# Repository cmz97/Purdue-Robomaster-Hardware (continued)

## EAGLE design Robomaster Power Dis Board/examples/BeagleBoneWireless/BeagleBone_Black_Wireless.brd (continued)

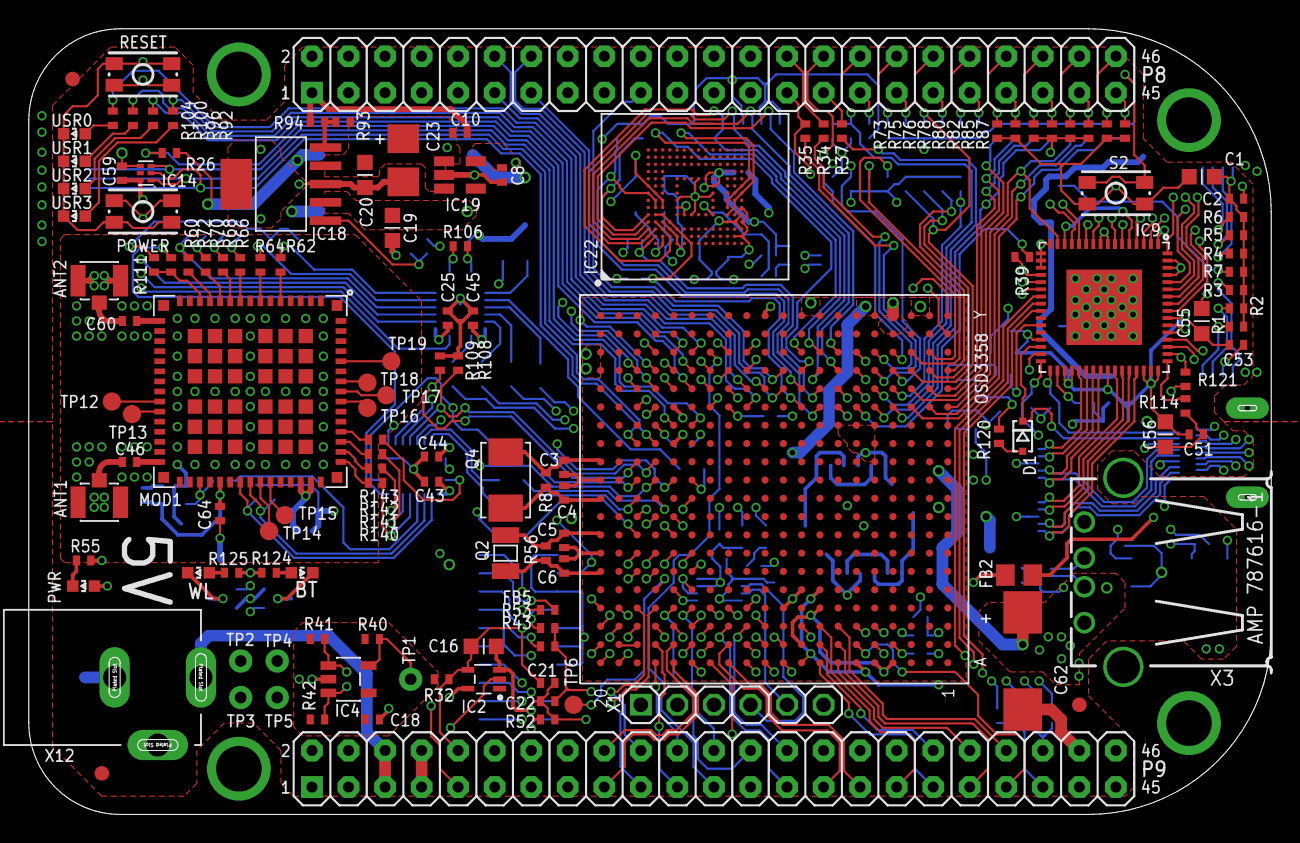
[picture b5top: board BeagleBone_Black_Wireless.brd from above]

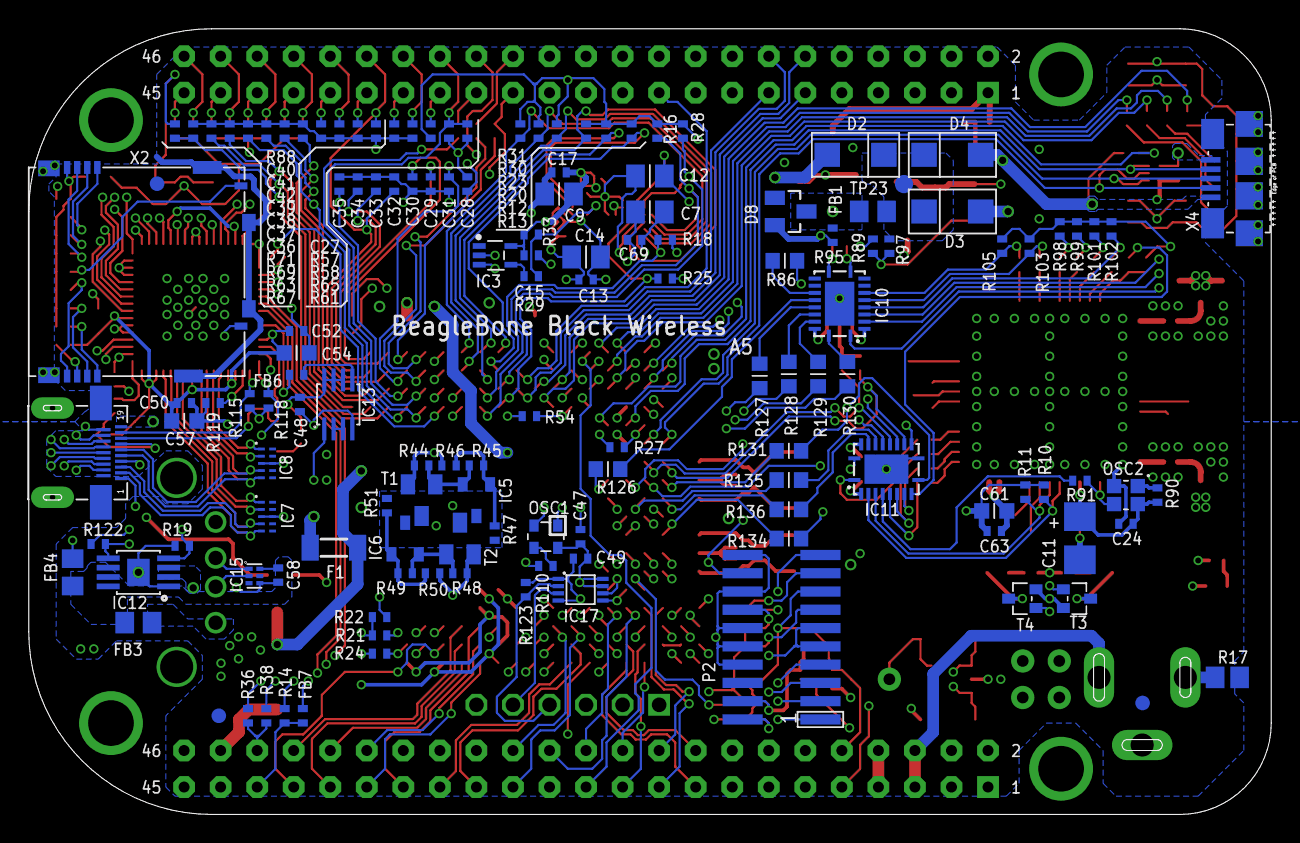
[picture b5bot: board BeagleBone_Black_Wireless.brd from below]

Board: 6 copper layers, 86.4 x 54.6 mm, 275 parts (139 on the bottom side), 262 nets.

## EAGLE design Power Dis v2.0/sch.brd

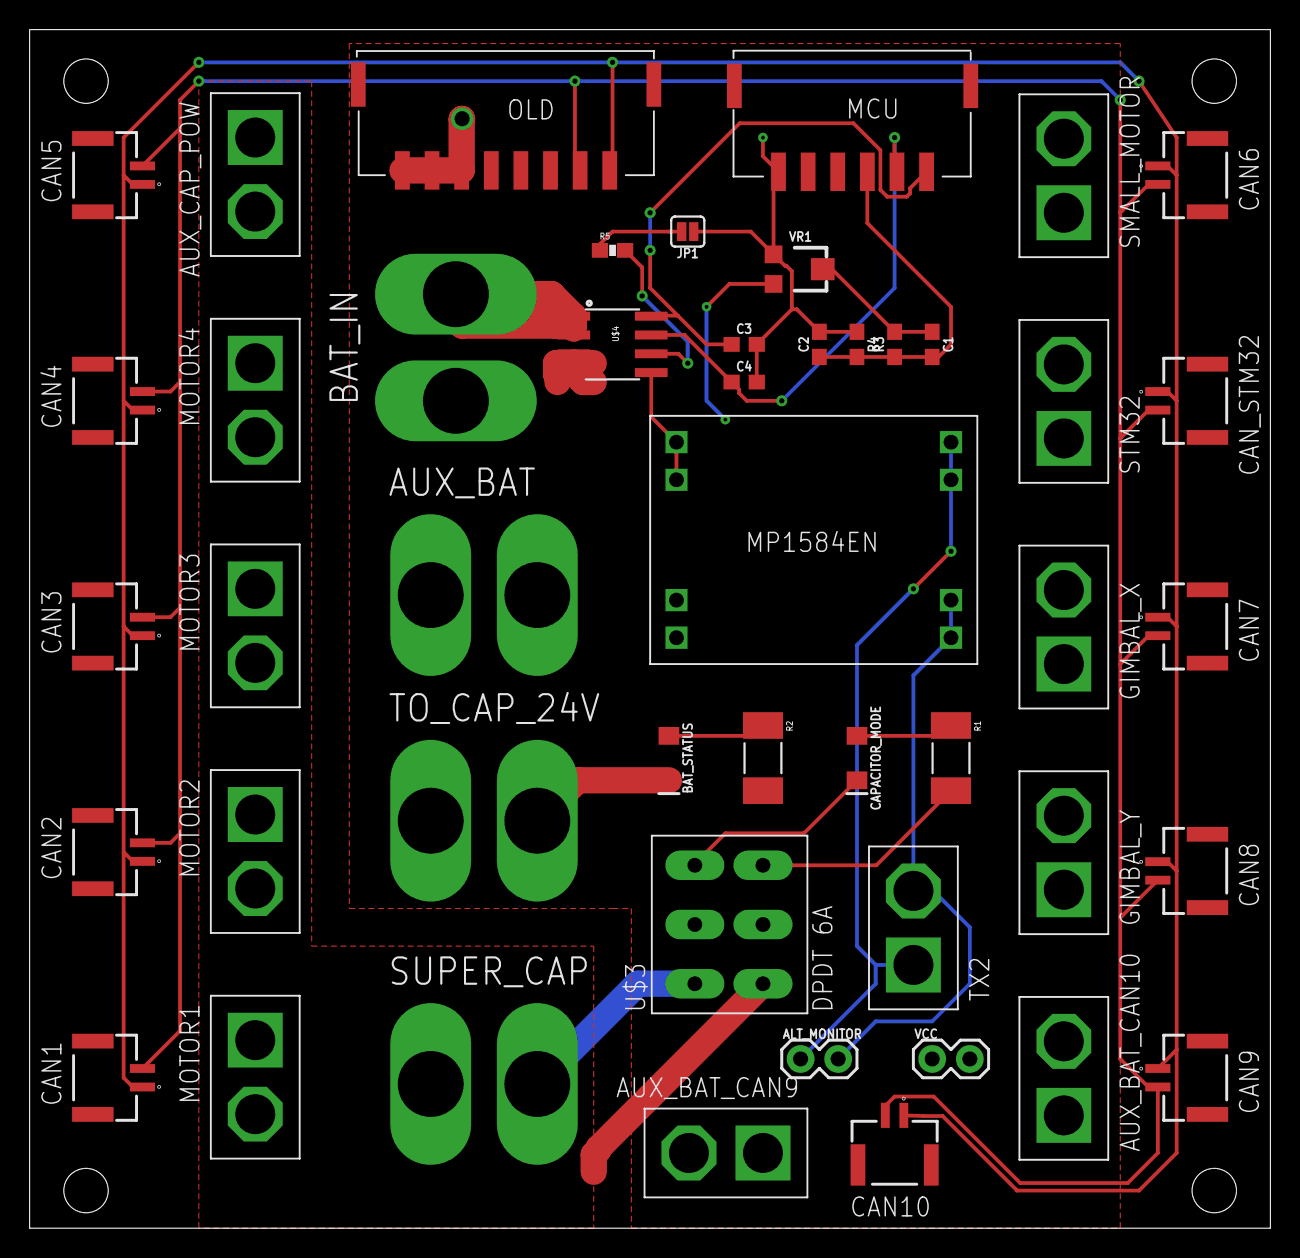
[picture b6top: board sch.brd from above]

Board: 2 copper layers, 83.8 x 81.0 mm, 47 parts (0 on the bottom side), 19 nets.

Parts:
ALT_MONITOR: 1X02
AUX_BAT: XT60
AUX_BAT_CAN9, AUX_BAT_CAN10: XT30
AUX_CAP_POW: XT30
BAT_IN: XT60
BAT_STATUS: 3V 20mA; LED-1206
C1, C2, C3: 0.1uF; 0603
C4: 1nF; 0603
CAN1, CAN2, CAN3, CAN4, CAN5, CAN6, CAN7, CAN8, CAN9, CAN10: BM02B-GHS-TBT(LF)(SN); BM02B-GHS-TBT_1
CAN_STM32: BM02B-GHS-TBT(LF)(SN); BM02B-GHS-TBT_1
CAPACITOR_MODE: 3V 20mA; LED-1206
GIMBAL_X: XT30
GIMBAL_Y: XT30
JP1: JUMPER-SMT_2_NO_SILK; SMT-JUMPER_2_NO_SILK
MCU: S6B-PH-SM4_TB
MOTOR1, MOTOR2, MOTOR3, MOTOR4: XT30
OLD: S8B-PH-SM4_TB
R1, R2: 1.2K; R2010
R3: 10k; 0603
R4: 2.0k; 0603
R5: 4.7K; 0603-RES
SMALL_MOTOR: XT30
STM32: XT30
SUPER_CAP: XT60
TO_CAP_24V: XT60
TX2: XT30
U$2: MP1584; MP1584_AMAZON
U$3: DPDT
U$4: ACS723; SO08
VCC: 1X02
VR1: 10k; TRIMPOT-SMD-TC33X

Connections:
ALT_GND: ALT_MONITOR.1, TX2.P$1, U$2.5, U$2.6
ALT_VCC: ALT_MONITOR.2, TX2.P$2, U$2.7, U$2.8
ANALOG_OUT: C1.2, C2.1, MCU.3, R3.1, R4.2
BAT_24V: AUX_BAT.1, AUX_BAT_CAN9.P$2, AUX_BAT_CAN10.P$2, GIMBAL_X.P$2, GIMBAL_Y.P$2, OLD.3, OLD.4, OLD.5, R2.2, SMALL_MOTOR.P$2, STM32.P$2, TO_CAP_24V.1, U$2.3, U$2.4, U$3.P$2, U$4.3, U$4.4, VCC.2, VR1.3
BAT_GND: AUX_BAT.2, AUX_BAT_CAN9.P$1, AUX_BAT_CAN10.P$1, BAT_IN.2, BAT_STATUS.C, C2.2, C3.2, C4.2, GIMBAL_X.P$1, GIMBAL_Y.P$1, JP1.1, MCU.6, OLD.6, OLD.7, OLD.8, R4.1, SMALL_MOTOR.P$1, STM32.P$1, TO_CAP_24V.2, U$2.1, U$2.2, U$3.P$5, U$4.5, VCC.1, VR1.1
BAT_IN: BAT_IN.1, U$4.1, U$4.2
BW_SEL: R5.2, U$4.6
CANH: CAN1.2, CAN2.2, CAN3.2, CAN4.2, CAN5.2, CAN6.2, CAN7.2, CAN8.2, CAN9.2, CAN10.2, CAN_STM32.2, OLD.2
CANL: CAN1.1, CAN2.1, CAN3.1, CAN4.1, CAN5.1, CAN6.1, CAN7.1, CAN8.1, CAN9.1, CAN10.1, CAN_STM32.1, OLD.1
CAP_24V: AUX_CAP_POW.P$2, MOTOR1.P$2, MOTOR2.P$2, MOTOR3.P$2, MOTOR4.P$2, SUPER_CAP.1, U$3.P$1
CAP_GND: AUX_CAP_POW.P$1, MOTOR1.P$1, MOTOR2.P$1, MOTOR3.P$1, MOTOR4.P$1, SUPER_CAP.2, U$3.P$4
MCU_VCC: C3.1, MCU.1, U$4.8
unnamed: R1.2, U$3.P$3
unnamed: CAPACITOR_MODE.A, R1.1
unnamed: CAPACITOR_MODE.C, U$3.P$6
unnamed: JP1.2, R5.1
unnamed: BAT_STATUS.A, R2.1
unnamed: C1.1, R3.2, VR1.2
VIOUT: C4.1, MCU.2, U$4.7

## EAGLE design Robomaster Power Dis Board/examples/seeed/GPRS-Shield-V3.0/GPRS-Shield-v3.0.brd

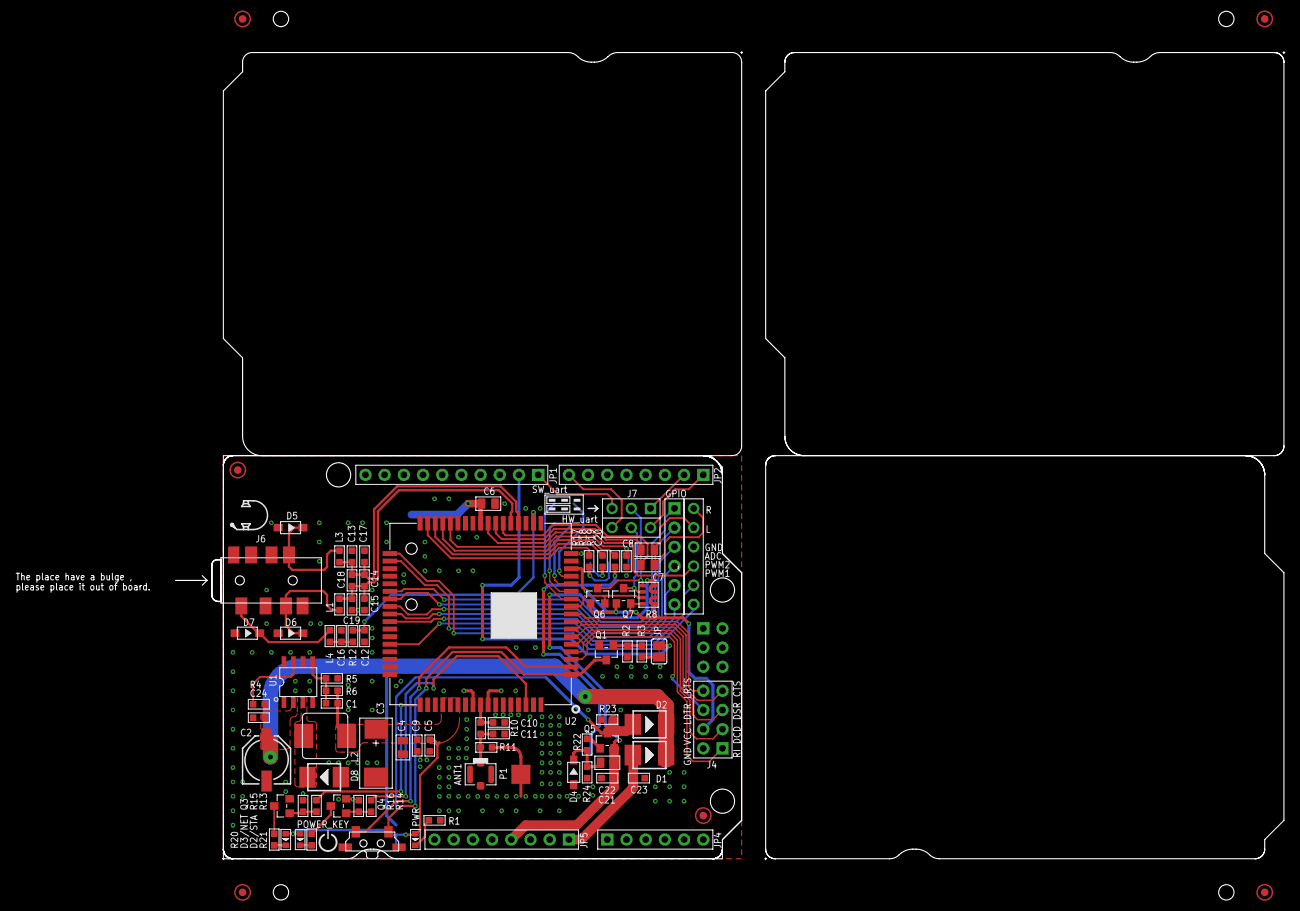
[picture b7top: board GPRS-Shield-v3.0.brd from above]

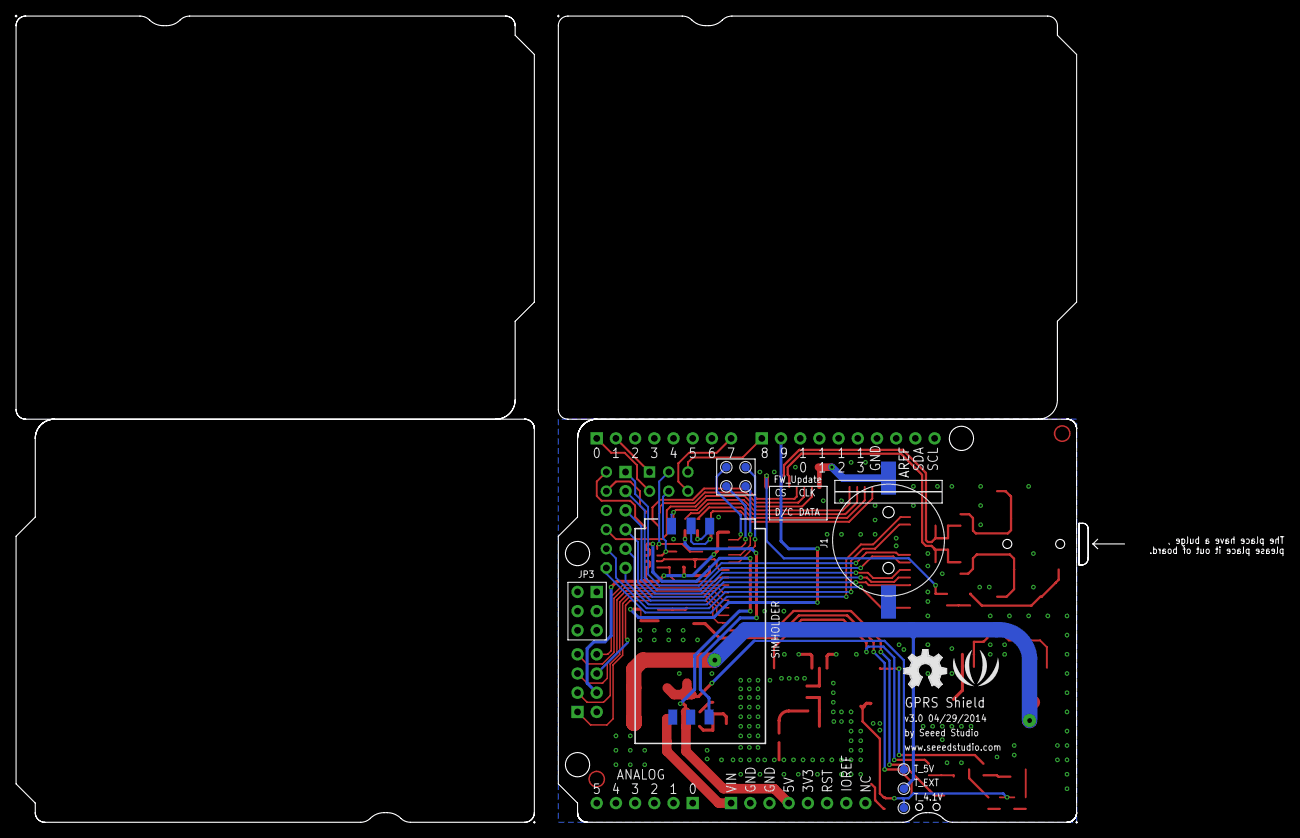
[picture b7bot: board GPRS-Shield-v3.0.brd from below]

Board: 2 copper layers, 146.8 x 106.9 mm, 95 parts (11 on the bottom side), 74 nets.

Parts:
ANT1: 4P-U-FL
C1, C10, C11: DNP; C0603
C2: 16V 220uF; ELECTRO-SMD-D-5.6MM
C3: 470uF; AVX-D
C4, C22: 10uF; C0805
C5, C9, C21, C23, C24: 100nF; C0603
C6: 4.7u; C0805
C7, C8: 2.2u; C0805
C12, C16, C17, C18, C19: 39pF; C0603
C13, C14, C15: 8.2pF; C0603
C20: 100n; C0603
CLK: TP_4545
CS: TP_4545
D1, D2, D8: SS54; SMB
D2/STA: red; D0603
D3/NET: green; D0603
D4: MBR0520; SOD123-2.7X1.6
D5, D6, D7: CESD5V0D1; SOD123-2.7X1.6
D/C: TP_4545
DATA: TP_4545
J1: SMD-CR1220-2
J3: 6P-2.54-65/35MIL
J4: 2X4P-2.54
J6: 8P-SMD-3.5
J7: CK_2X3_DD; CK_2X3
J13: CK_1X6
JP: 2P-SMD-3.3X2
L1, L3, L4: 120R 500mA; L0603
L2: 10uH; L0630
P1: JP
P2, P3, P4, P5, P6, P7: ROUND-MARK-1.0
POWER_KEY: BUTTON-4P-REINFORCE'TS-118E'; 4P-SMD-7X3.5X3.5H
PWR: green; D0603
Q1, Q3, Q4: 9013; SOT23
Q5: SI2305DS; SOT23
Q6, Q7: BSN20; SOT23
R1: 1k; R0603
R2, R15, R16: 47k; R0603
R3, R13, R14: 4.7k; R0603
R4: 100k; R0603
R5: 10k 1%; R0603
R6: 24k 1%; R0603
R8: 4.7k; 1206-8-3.3X2.4
R10: 0R; R0603
R11: DNP; R0603
R12: 68R; R0603
R17, R18, R19: 22R; R0603
R20, R21: 470R; R0603
R22: 100R; R0603
R23, R24: 1M; R0603
SIMHOLDER: SIMHOLDER3
T_4.1V, T_5V: TP_4545
T_EXT: TP_4545
U1: TD1410; SOP8
U2: SIM900
U4: ARDUINO-38P-500519002
U$26: LOGO_SILK
U$28: OSHW_FILLX200_NOTEXT

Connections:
5V: C21.2, C22.2, Q5.2, R8.7, R8.8, U4.28
ADC: J13.3, U2.25
CTS: J4.4, U2.7
D9: JP.1, JP.2, R3.1, U4.10
DCD: J4.2, U2.5
DISP_CLK: CLK.T, U2.11
DISP_CS: CS.T, U2.14
DISP_D/C: D/C.T, U2.13
DISP_DATA: DATA.T, U2.12
DSR: J4.3, U2.6
EXT_VIN: C23.2, D1.+, U4.25
GND: ANT1.GND1, ANT1.GND2, ANT1.GND3, C2.-, C3.-, C4.1, C5.1, C6.1, C9.1, C10.1, C11.1, C12.2, C13.2, C15.1, C16.1, C17.2, C19.1, C20.2, C21.1, C23.1, C24.1, D4.1, D5.1, D6.1, D7.1, D8.+, J1.-, J4.8, J6.2, J13.4, P1.2, POWER_KEY.S1, POWER_KEY.S2, Q1.2, Q3.2, Q4.2, R1.1, R2.2, R5.2, R15.2, R16.2, R23.2, R24.2, SIMHOLDER.6, U1.4, U2.17, U2.18, U2.20, U2.29, U2.39, U2.45, U2.46, U2.53, U2.54, U2.58, U2.59, U2.61, U2.62, U2.63, U2.64, U2.65, U4.15, U4.26, U4.27
GPIO1: J3.1, U2.40
GPIO2: J3.2, U2.41
GPIO3: J3.3, U2.42
GPIO4: J3.4, U2.43
GPIO5: J3.5, U2.44
GPIO6: J3.6, U2.47
HRXD: J7.2, Q6.3, R8.1
HTXD: J7.5, Q7.3, R8.2
LDTR: J4.6, U2.3
LINEIN_L: C8.2, U2.24
LINEIN_R: C7.2, U2.23
LRTS: J4.5, U2.8
LRXD: Q6.2, R8.3, U2.10
LTXD: Q7.2, R8.4, U2.9
MRXD: J7.1, U4.2
MTXD: J7.6, U4.1
unnamed: C10.2, R10.2, U2.60
unnamed: D2.+, Q5.3, R23.1, T_5V.T
unnamed: Q3.3, R20.2
unnamed: R19.2, SIMHOLDER.4
unnamed: R18.1, SIMHOLDER.3
unnamed: R17.1, SIMHOLDER.2
unnamed: D3/NET.-, R20.1
unnamed: Q3.1, R13.2, R15.1
unnamed: PWR.-, R1.2
unnamed: R13.1, U2.52
unnamed: POWER_KEY.1, U2.2
unnamed: R4.1, U1.7
unnamed: C12.1, R12.1, U2.19
unnamed: C13.1, C14.2, C17.1, C18.2, L3.1, U2.21
unnamed: Q4.3, R21.2
unnamed: D2/STA.-, R21.1
unnamed: Q4.1, R14.2, R16.1
unnamed: C14.1, C15.2, C18.1, C19.2, L1.1, U2.22
unnamed: R14.1, U2.66
unnamed: ANT1.D, C11.2, R10.1, R11.2
unnamed: C7.1, J13.6
unnamed: C8.1, J13.5
unnamed: C16.2, L4.1, R12.2
unnamed: Q5.1, R22.1
unnamed: Q1.1, R2.1, R3.2
unnamed: D8.-, L2.1, U1.3
unnamed: C22.1, D4.2, R22.2, R24.1
unnamed: D7.2, J6.1, L4.2
unnamed: C1.2, R5.1, R6.1, U1.5
unnamed: D5.2, J6.4, L3.2
unnamed: D6.2, J6.3, L1.2
unnamed: P1.1, R11.1
PWM1: J13.1, U2.35
PWM2: J13.2, U2.36
PWRKEY: POWER_KEY.2, Q1.3, U2.1
RI: J4.1, U2.4
SIM_CLK: R18.2, U2.32
SIM_DATA: R19.1, U2.31
SIM_RST: R17.2, U2.33
SIM_VDD: C20.1, SIMHOLDER.1, U2.30
SRXD: J7.3, U4.9
STXD: J7.4, U4.8
VBAT: C1.1, C3.+, C4.2, C5.2, C9.2, D2/STA.+, D3/NET.+, L2.2, PWR.+, R6.2, T_4.1V.T, U2.55, U2.56, U2.57
VDD_EXT: J4.7, Q6.1, Q7.1, R8.5, R8.6, U2.15
VIN: C2.+, C24.2, D1.-, D2.-, R4.2, T_EXT.T, U1.2
VRTC: C6.2, J1.+, U2.26

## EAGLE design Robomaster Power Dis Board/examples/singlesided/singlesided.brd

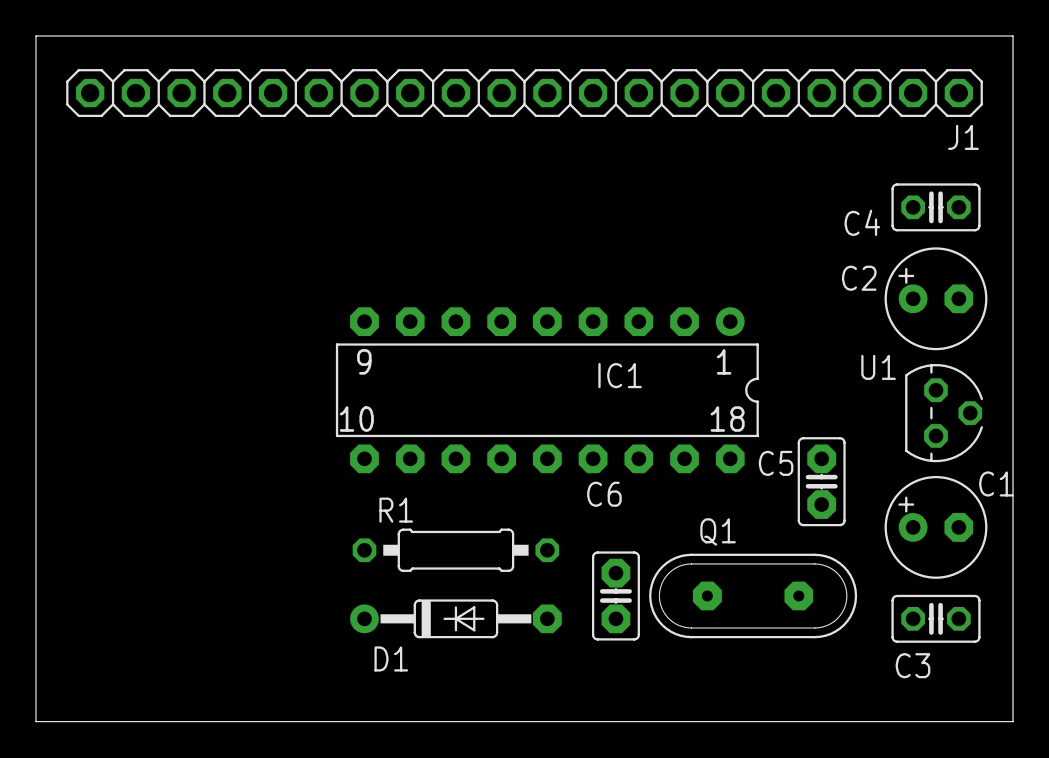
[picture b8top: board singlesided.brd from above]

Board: 2 copper layers, 54.3 x 38.1 mm, 12 parts (0 on the bottom side), 20 nets, no tracks yet.

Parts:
C1, C2: 10u; E2,5-6
C3, C4: 10n; C025-025X050
C5, C6: 27p; C2,5-2
D1: 1N4148; DO35-10
IC1: 16F84; DIL18
J1: 1X20
Q1: QS
R1: 2.2k; 0207/10
U1: 78L05; TO92

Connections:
+12V: C1.+, C3.2, J1.2, U1.3
A0: IC1.17, J1.4
A1: IC1.18, J1.5
A2: IC1.1, J1.6
A3: IC1.2, J1.7
A4: IC1.3, J1.8
B0: IC1.6, J1.9
B1: IC1.7, J1.10
B2: IC1.8, J1.11
B3: IC1.9, J1.12
B4: IC1.10, J1.13
B5: IC1.11, J1.14
B6: IC1.12, J1.15, J1.18
B7: IC1.13, J1.16, J1.17
GND: C1.-, C2.-, C3.1, C4.1, C5.1, C6.1, IC1.5, J1.1, J1.20, U1.2
unnamed: D1.K, IC1.4, J1.19
unnamed: D1.A, R1.1
unnamed: C5.2, IC1.16, Q1.2
unnamed: C6.2, IC1.15, Q1.1
VCC: C2.+, C4.2, IC1.14, J1.3, R1.2, U1.1

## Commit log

2018-10-21 new upload
2018-11-03 add image
2019-01-20 added power dis 2.1
2019-07-18 shit
